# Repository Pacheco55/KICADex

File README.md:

# KICADex

Ejercicios y modulos PCB en kicad muchos hasta con archivo GERBER

## **Soporte**

¿Necesitas ayuda? ¡Estamos aquí para ti!

**Reportar Bugs**: Abre un issue en GitHub

**Sugerencias**: Discussions en el repositorio

**Contacto**: info@pixelbits.studio

---

## **Créditos**

### **Desarrollo Principal**

**PIXELBITS Studios**
*Innovación en tecnología embebida*

### **Lead Developer**

**Pacheco 55**
*Arquitecto de software*

---

## **Licencia**

Este proyecto está licenciado bajo la Licencia MIT - ver el archivo [LICENSE](LICENSE) para más detalles.

---

## **¡Apóyanos!**

Si este proyecto te ha sido útil:

Dale una estrella al repositorio, compártelo con otros developers, déjanos tus comentarios y contribuye al proyecto.

---

<div align="center">

### **Hecho con amor por PIXELBITS Studios**

*Transformando ideas en código, un circuito a la vez.*

**[Instagram](https://www.instagram.com/pixelbits_studios/) | [YouTube](https://www.youtube.com/channel/UCkLUjIeYTECtigFdcQjWu5Q) | [Twitter](https://x.com/pixelbitstud) | [Twitch](https://www.twitch.tv/pixelbits_studio/about)**

---

*KiCAD exercises - Porque conocer tu entorno es el primer paso hacia la integridad.*

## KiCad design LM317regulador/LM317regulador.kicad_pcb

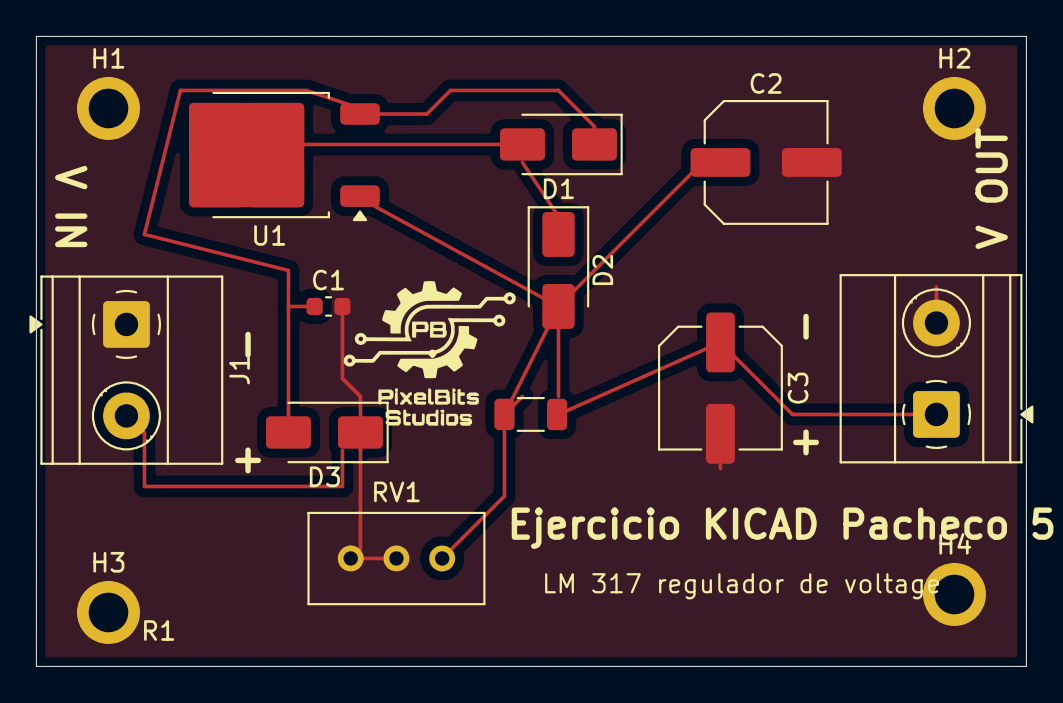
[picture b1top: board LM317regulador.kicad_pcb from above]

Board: 2 copper layers, 55.0 x 35.0 mm, 16 parts (0 on the bottom side), 5 nets.

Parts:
.: LOGO; PBSlogo10x10
C1: C; C_0603_1608Metric
C2, C3: C_Polarized; C_Elec_6.3x5.8
D1, D2, D3: D; D_SMA
H1, H2, H3, H4: MountingHole_2.2mm_M2_ISO7380_Pad
J1, J2: Screw_Terminal_01x02; TerminalBlock_Phoenix_MKDS-1,5-2-5.08_1x02_P5.08mm_Horizont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
R1: R_US; R_1206_3216Metric
RV1: R_Potentiometer_Trim_US; Potentiometer_Bourns_3296W_Vertical
U1: LM317_TO-252; TO-252-2

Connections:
GND: C1.2, C2.2, C3.2, H1.1, H2.1, H3.1, H4.1, J1.1, J2.2, RV1.2, RV1.3
unnamed: C3.1, D1.2 (A), D2.1 (K), J2.1, R1.1, U1.2 (VO)
unnamed: C1.1, D1.1 (K), D3.2 (A), U1.3 (VI)
unnamed: C2.1, D2.2 (A), R1.2, RV1.1, U1.1 (ADJ)
unnamed: D3.1 (K), J1.2

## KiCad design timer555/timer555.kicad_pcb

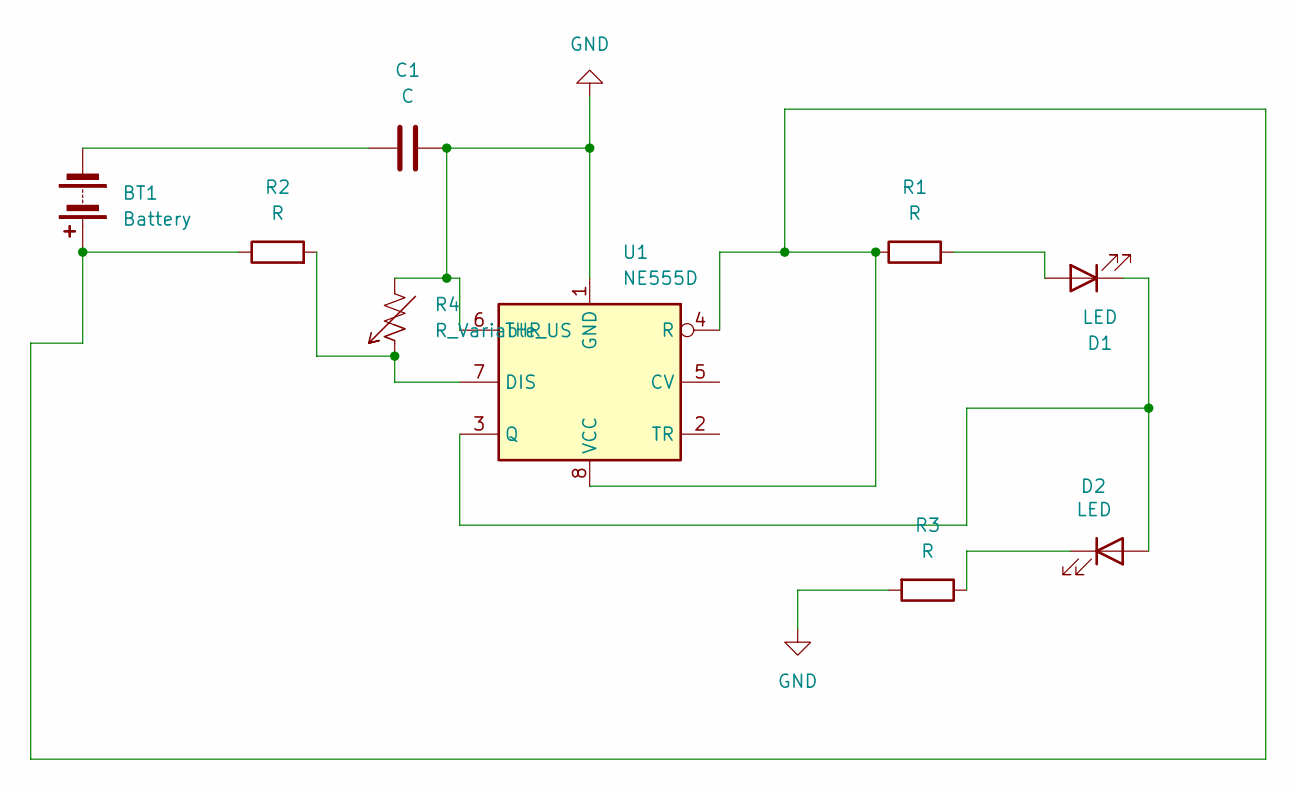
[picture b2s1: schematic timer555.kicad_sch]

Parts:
BT1: Battery; BatteryHolder_Eagle_12BH611-GR
C1: C; CP_Elec_4x4.5
D1, D2: LED; LED_1206_3216Metric
R1, R2, R3: R; R_0402_1005Metric_Pad0.72x0.64mm_HandSolder
R4: R_Variable_US; Potentiometer_Bourns_3299W_Vertical
U1: NE555D; SOIC-8_3.9x4.9mm_P1.27mm

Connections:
GND: C1.2, R3.2, R4.2, U1.1 (GND), U1.6 (THR)
unnamed: BT1.1 (+), R1.1, R2.1, U1.4 (R), U1.8 (VCC)
unnamed: BT1.2 (-), C1.1
unnamed: D1.2 (A), R1.2
unnamed: D1.1 (K), D2.2 (A), U1.3 (Q)
unnamed: D2.1 (K), R3.1
unnamed: R2.2, R4.1, U1.7 (DIS)

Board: 2 copper layers, 9 parts (0 on the bottom side), 7 nets, no tracks yet.

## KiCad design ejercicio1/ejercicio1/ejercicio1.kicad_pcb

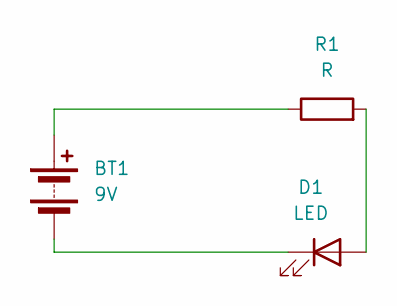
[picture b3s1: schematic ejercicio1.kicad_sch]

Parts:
BT1: 9V; PinSocket_2x01_P2.54mm_Vertical
D1: LED; LED_D5.0mm_FlatTop
R1: R; R_Axial_DIN0207_L6.3mm_D2.5mm_P7.62mm_Horizontal

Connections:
unnamed: BT1.1 (+), R1.1
unnamed: BT1.2 (-), D1.1 (K)
unnamed: D1.2 (A), R1.2

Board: 2 copper layers, 3 parts (0 on the bottom side), 3 nets, no tracks yet.
